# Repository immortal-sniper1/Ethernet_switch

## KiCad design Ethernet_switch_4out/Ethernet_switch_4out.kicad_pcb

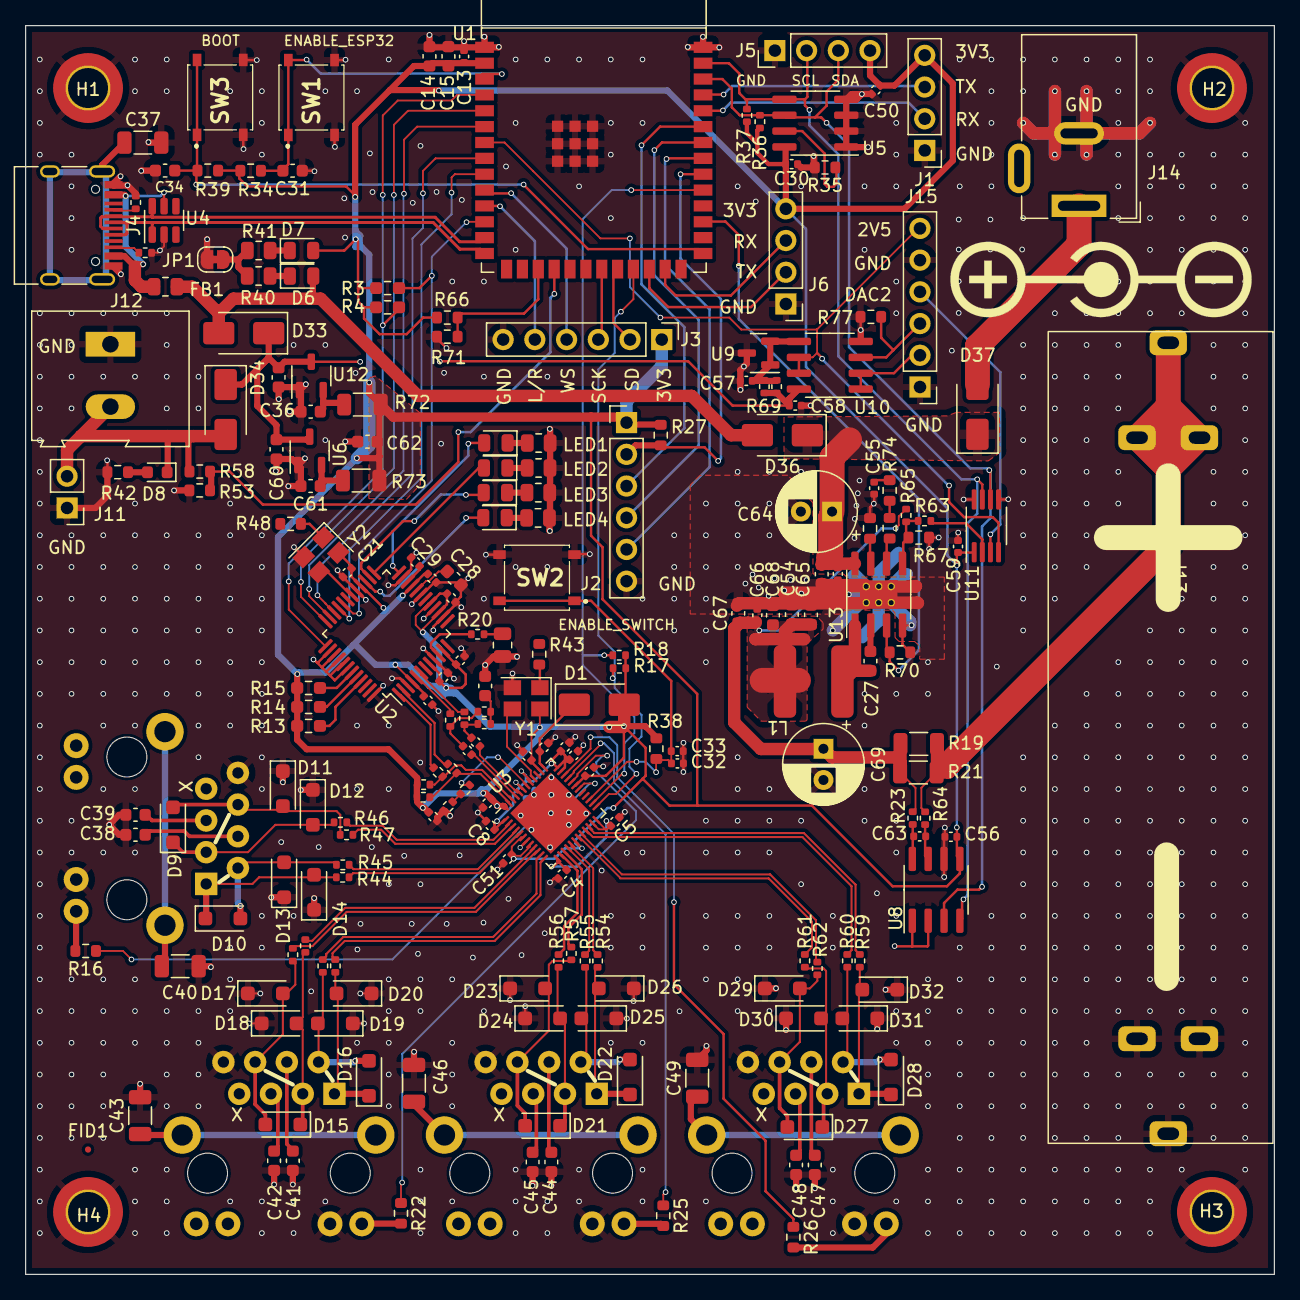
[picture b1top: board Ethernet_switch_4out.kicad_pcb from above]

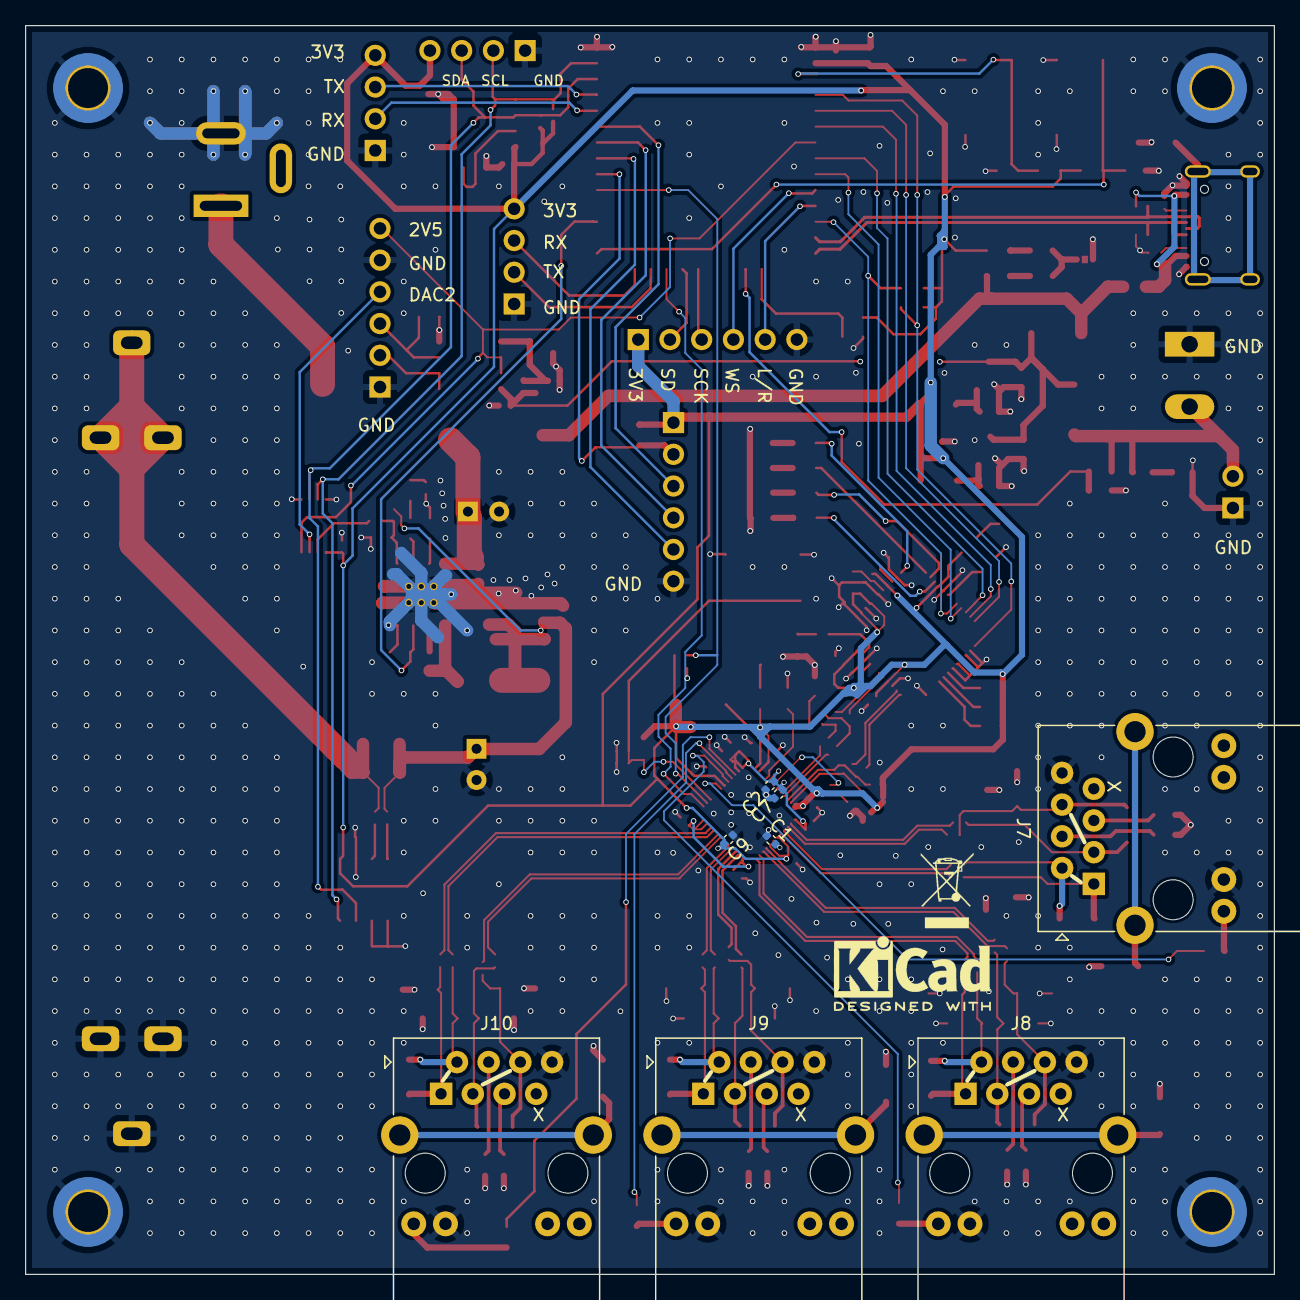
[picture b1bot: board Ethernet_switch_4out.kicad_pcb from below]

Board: 4 copper layers, 100.0 x 100.0 mm, 225 parts (10 on the bottom side), 151 nets.

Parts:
C1, C2, C3, C4, C5, C6, C7, C8, C9, C10, C11, C12, C13, C16, C17, C18, C19, C20, C21, C22, C25, C29, C30, C32, C33, C50, C51, C52, C56, C57, C58, C59, C66: 1u; C_0402_1005Metric
C14, C15, C28, C35, C36, C53, C54, C60, C61, C62, C65, C67, C68: 10u; C_0603_1608Metric
C23, C24: 6n8; C_0402_1005Metric
C26: 10n; C_0603_1608Metric
C27, C31, C34, C38, C39, C41, C42, C44, C45, C47, C48: 100n; C_0603_1608Metric
C37, C40, C43, C46, C49: 1n; C_1206_3216Metric
C55, C63: 4n7; C_0402_1005Metric
C64, C69: C_Polarized_Small; CP_Radial_D6.3mm_P2.50mm
D1, D33, D34, D36, D37: D_Schottky; D_SMA
D2, D3, D4, D5, D6, D7: green; LED_0805_2012Metric
D8: red; LED_0603_1608Metric
D9, D10, D11, D12, D13, D14, D15, D16, D17, D18, D19, D20, D21, D22, D23, D24, D25, D26, D27, D28, D29, D30, D31, D32: SMF6.0CA; D_SOD-123F
FB1: FerriteBead_Small; R_0805_2012Metric
FID1: Fiducial; Fiducial_0.5mm_Mask1mm
FID2: Fiducial; KiCad-Logo2_5mm_SilkScreen
FID3: Fiducial; WEEE-Logo_4.2x6mm_SilkScreen
FID4: Polarity; Polarity_Center_Positive_6mm_SilkScreen
H1, H2, H3, H4: hole; MountingHole_3.2mm_M3_DIN965_Pad_TopBottom
J1, J5, J6: Conn_01x04; PinHeader_1x04_P2.54mm_Vertical
J2, J3, J15: Conn_01x06; PinHeader_1x06_P2.54mm_Vertical
J4: USB_C_Receptacle; USB_C_Receptacle_HRO_TYPE-C-31-M-12
J7, J8, J9, J10: RJ45 Abracon ARJM11B1; RJ45_Abracon_ARJM11B1
J11: Conn_01x02; PinHeader_1x02_P2.54mm_Vertical
J12: Conn_01x02; TerminalBlock_Altech_AK300-2_P5.00mm
J13: Conn_01x02; MYOUNG MY-18650-01
J14: Jack-DC; BarrelJack_Wuerth_6941xx301002
JP1: Jumper_2_Bridged; SolderJumper-2_P1.3mm_Bridged_RoundedPad1.0x1.5mm
L1: 33u; SWPA6045S330MT
R1, R2, R9, R10: 49R9; R_0402_1005Metric
R3, R4, R13, R14, R15: 10k; R_0603_1608Metric_Pad0.98x0.95mm_HandSolder
R5, R6, R7, R8, R44, R45, R46, R47, R49, R50, R51, R52, R54, R55, R56, R57, R59, R60, R61, R62: 10; R_0402_1005Metric
R11, R69: 2k; R_0402_1005Metric
R12, R20, R68: 470; R_0402_1005Metric
R16, R22, R25, R26, R42: 1k; R_0603_1608Metric
R17, R18: 3k9; R_0402_1005Metric
R19, R21, R72, R73: 0R1; R_1206_3216Metric
R23, R64: 5R1; R_0402_1005Metric
R24: 12k; R_0805_2012Metric
R27, R34, R35, R38, R39, R53, R58, R66, R67, R70, R71, R74, R75: 10k; R_0603_1608Metric
R28, R29, R30, R31, R40, R41: 1k; R_0805_2012Metric
R32, R33, R36, R37: 5k1; R_0402_1005Metric
R43, R48: 2k; R_0603_1608Metric
R63, R65: 47k; R_0402_1005Metric
R76, R77: 120k; R_0603_1608Metric
SW1, SW2, SW3: MCU_RESET; PTS526SK15SMTR2LFS
U1: ESP32-S3-WROOM-1
U2: W5500; LQFP-48_7x7mm_P0.5mm
U3: RTL8305NB-VB-CG; QFN-48-1EP_6x6mm_P0.4mm_EP4.6x4.6mm
U4: SRV05-4; SOT-23-6
U5: CAT24C256; SOIC-8_3.9x4.9mm_P1.27mm
U6, U12: XC6206PxxxMR; SOT-23-3
U8: INA219AxD; SOIC-8_3.9x4.9mm_P1.27mm
U9: CJ431; SOT-23
U10: MCP6002-xSN; SOIC-8_3.9x4.9mm_P1.27mm
U11: AD5337; MSOP-8_3x3mm_P0.65mm
U13: RT7272B; SOIC-8-1EP_3.9x4.9mm_P1.27mm_EP2.29x3mm_ThermalVias
Y1, Y2: 25MHz; Crystal_SMD_3225-4Pin_3.2x2.5mm

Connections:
1V2: C1.2, C2.2, C3.2, C4.2, C5.2, C6.2, C7.2, C8.2, U3.1 (AVDDL), U3.7 (DVDDL), U3.13 (AVDDL), U3.23 (AVDDL), U3.24 (DVDDL), U3.35 (DVDDL), U3.36 (V12OUT), U3.41 (AVDDLPLL), U3.43 (AVDDL)
+3V3: C9.2, C10.2, C11.2, C12.2, C13.2, C14.1, C15.1, C17.2, C18.2, C19.2, C20.2, C21.2, C22.2, C25.2, C30.2, C50.2, C51.2, C56.2, C59.2, C62.1, D1.2 (A), D7.2 (A), J1.4, J2.1, J3.1, J5.4, J6.4, R1.2, R2.2, R3.1, R4.1, R13.2, R14.2, R15.2, R17.1, R18.1, R27.1, R34.1, R36.1, R37.1, R38.2, R39.2, R66.1, R72.1, R73.1, U1.2 (3V3), U2.4 (AVDD), U2.8 (AVDD), U2.11 (AVDD), U2.15 (AVDD), U2.17 (AVDD), U2.21 (AVDD), U2.28 (VDD), U3.6 (AVDDH), U3.8 (AVDDH), U3.18 (AVDDH), U3.31 (DVDDH), U3.38 (AVDDHPLL), U3.48 (AVDDH), U5.8 (VCC), U8.5 (VS), U11.1 (VDD), Y1.4, Y2.4
+5V: D6.2 (A), D33.2 (A), D36.2 (A), FB1.1
+BATT: D8.1 (K), D34.2 (A), J11.2, J12.2, R58.1
+VDC: C35.1, C58.2, C60.1, D33.1 (K), D34.1 (K), R68.2, R69.1, U6.3 (VI), U10.8 (V+), U12.3 (VI)
/2V5_RAW: C57.2, R68.1, R69.2, U9.1 (REF), U9.2 (K), U10.5 (+)
/Cell/BUCK_EN: R70.1, U1.29 (SPIIO7/GPIO36/FSPICLK/SUBSPICLK), U13.3 (EN)
/Cell/Buck_out: C54.1, C65.1, C66.2, C67.1, C68.1, C69.1, L1.2, R19.1, R21.1, R23.1, R65.2
/Cell/DAC1: R63.1, U11.2 (Vout_A)
/Cell/DAC2: J15.4, U11.3 (Vout_B)
/Cell/FB: R63.2, R65.1, R67.1, U13.5 (FB)
/Cell/Rlim: R76.1, U13.7 (RLIM)
/Cell/SW: C27.1, L1.1, U13.1 (SW)
/Cell/Vin_buck: C52.2, C53.1, C64.1, D36.1 (K), D37.1 (K), U13.8 (VIN)
/Cell/boot: C27.2, U13.2 (BOOT)
/Cell_V: R53.1, R58.2, U1.18 (GPIO10/TOUCH10/ADC1_CH9/FSPICS0/FSPIIO4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)
/ESP_BOOT: C34.1, R39.1, SW3.1 (A), U1.27 (GPIO0/BOOT)
/ESP_EN: C31.2, R34.2, SW1.1 (A), U1.3 (EN)
/L/R: J3.5, U1.11 (GPIO18/U1RXD/ADC2_CH7/CLK_OUT3)
/MISO: U1.8 (GPIO15/U0RTS/ADC2_CH4/XTAL_32K_P), U2.34 (MISO)
/MOSI: U1.6 (GPIO6/TOUCH6/ADC1_CH5), U2.35 (MOSI)
/Output_port1/GREEN: J8.9 (LEDG_A), R22.2
/Output_port1/L_RD+: D15.1 (A1), D18.2 (A2), J8.3 (RD+), R51.2
/Output_port1/L_RD-: D15.2 (A2), D17.2 (A2), J8.6 (RD-), R52.2
/Output_port1/L_TD+: D16.1 (A1), D20.2 (A2), J8.1 (TD+), R49.2
/Output_port1/L_TD-: D16.2 (A2), D19.2 (A2), J8.2 (TD-), R50.2
/Output_port1/RD+: R51.1, U3.9 (TXOP2)
/Output_port1/RD-: R52.1, U3.10 (TXON2)
/Output_port1/TD+: R49.1, U3.12 (RXOP2)
/Output_port1/TD-: R50.1, U3.11 (RXON2)
/Output_port2/GREEN: J9.9 (LEDG_A), R25.2
/Output_port2/L_RD+: D21.1 (A1), D24.2 (A2), J9.3 (RD+), R56.2
/Output_port2/L_RD-: D21.2 (A2), D23.2 (A2), J9.6 (RD-), R57.2
/Output_port2/L_TD+: D22.1 (A1), D26.2 (A2), J9.1 (TD+), R54.2
/Output_port2/L_TD-: D22.2 (A2), D25.2 (A2), J9.2 (TD-), R55.2
/Output_port2/RD+: R56.1, U3.14 (RXIP3)
/Output_port2/RD-: R57.1, U3.15 (RXIN3)
/Output_port2/TD+: R54.1, U3.17 (TXOP3)
/Output_port2/TD-: R55.1, U3.16 (TXON3)
/Output_port3/GREEN: J10.9 (LEDG_A), R26.2
/Output_port3/L_RD+: D27.1 (A1), D30.2 (A2), J10.3 (RD+), R61.2
/Output_port3/L_RD-: D27.2 (A2), D29.2 (A2), J10.6 (RD-), R62.2
/Output_port3/L_TD+: D28.1 (A1), D32.2 (A2), J10.1 (TD+), R59.2
/Output_port3/L_TD-: D28.2 (A2), D31.2 (A2), J10.2 (TD-), R60.2
/Output_port3/RD+: R61.1, U3.19 (TXOP4)
/Output_port3/RD-: R62.1, U3.20 (TXON4)
/Output_port3/TD+: R59.1, U3.22 (RXOP4)
/Output_port3/TD-: R60.1, U3.21 (RXON4)
/Output_port/GREEN: J7.9 (LEDG_A), R16.2
/Output_port/L_RD+: D9.1 (A1), D12.2 (A2), J7.3 (RD+), R46.2
/Output_port/L_RD-: D9.2 (A2), D11.2 (A2), J7.6 (RD-), R47.2
/Output_port/L_TD+: D10.1 (A1), D14.2 (A2), J7.1 (TD+), R44.2
/Output_port/L_TD-: D10.2 (A2), D13.2 (A2), J7.2 (TD-), R45.2
/Output_port/RD+: R46.1, U3.2 (RXIP1)
/Output_port/RD-: R47.1, U3.3 (RXIN1)
/Output_port/TD+: R44.1, U3.5 (TXIP1)
/Output_port/TD-: R45.1, U3.4 (TXIN1)
/Rail_V: R66.2, R71.1, U1.17 (GPIO9/TOUCH9/ADC1_CH8/FSPIHD/SUBSPIHD)
/SCK: J3.3, U1.21 (GPIO13/TOUCH13/ADC2_CH2/FSPIQ/FSPIIO7/S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)
/SCLK: U1.9 (GPIO16/U0CTS/ADC2_CH5/XTAL_32K_N), U2.33 (SCLK)
/SD: J3.2, U1.22 (GPIO14/TOUCH14/ADC2_CH3/FSPIWP/FSPIDQS/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)
/SWITCH_EN: C32.2, C33.2, R38.1, SW2.1 (A), U3.27 (RESET_B)
/W5500_LED1: D5.2 (A), U2.24 (SPDLED)
/W5500_LED2: D4.2 (A), U2.25 (LINKLED)
/W5500_LED3: D3.2 (A), U2.26 (DUPLED)
/W5500_LED4: D2.2 (A), U2.27 (ACTLED)
/WS: J3.4, U1.10 (GPIO17/U1TXD/ADC2_CH6)
/cc1: J4.A5 (CC1), R32.1
/cc2: J4.B5 (CC2), R33.1
/green_LED1: R16.1, U3.30 (P1LED)
/green_LED2: R22.1, U3.32 (P2LED/DIS_RST_BLNK)
/green_LED3: R25.1, U3.33 (P3LED)
/green_LED4: R26.1, U3.34 (P4LED)
/~INT: U1.5 (GPIO5/TOUCH5/ADC1_CH4), U2.36 (~INT)
/~RST: R4.2, U1.4 (GPIO4/TOUCH4/ADC1_CH3), U2.37 (~RST)
/~SCS: R3.2, U1.12 (GPIO8/TOUCH8/ADC1_CH7/SUBSPICS1), U2.32 (~SCS)
CLK_EXT: J2.3, U1.35 (MTMS/GPIO42)
D+: J4.A6 (D+), J4.B6 (D+), U1.14 (GPIO20/U1CTS/ADC2_CH9/CLK_OUT1/USB_D+), U4.1 (IO1)
D-: J4.A7 (D-), J4.B7 (D-), U1.13 (GPIO19/U1RTS/ADC2_CH8/CLK_OUT2/USB_D-), U4.6 (IO4)
GND: C1.1, C2.1, C3.1, C4.1, C5.1, C6.1, C7.1, C8.1, C9.1, C10.1, C11.1, C12.1, C13.1, C14.2, C15.2, C16.1, C17.1, C18.1, C19.1, C20.1, C21.1, C22.1, C25.1, C26.1, C28.1, C29.1, C30.1, C31.1, C32.1, C33.1, C34.2, C35.2, C36.2, C37.2, C38.1, C39.1, C40.2, C41.1, C42.1, C43.2, C44.1, C45.1, C46.2, C47.1, C48.1, C49.2, C50.1, C51.1, C52.1, C53.2, C54.2, C55.2, C56.1, C57.1, C58.1, C59.1, C60.2, C61.2, C62.2, C64.2, C65.2, C66.1, C67.2, C68.2, C69.2, D11.1 (A1), D12.1 (A1), D13.1 (A1), D14.1 (A1), D17.1 (A1), D18.1 (A1), D19.1 (A1), D20.1 (A1), D23.1 (A1), D24.1 (A1), D25.1 (A1), D26.1 (A1), D29.1 (A1), D30.1 (A1), D31.1 (A1), D32.1 (A1), H1.1, H2.1, H3.1, H4.1, J1.1, J2.6, J3.6, J4.A1 (GND), J4.A12 (GND), J4.B1 (GND), J4.B12 (GND), J5.1, J6.1, J7.8 (GND), J7.10 (LEDG_K), J8.8 (GND), J8.10 (LEDY_K), J9.8 (GND), J9.10 (LEDY_K), J10.8 (GND), J10.10 (LEDY_K), J11.1, J12.1, J13.2, J14.2, J15.1, J15.5, JP1.1 (A), R11.1, R24.2, R28.2, R29.2, R30.2, R31.2, R32.2, R33.2, R35.2, R42.1, R53.2, R67.2, R70.2, R71.2, R76.2, R77.2, SW1.2 (B), SW2.2 (B), SW3.2 (B), U1.1 (GND), U1.40 (GND), U1.41 (GND), U2.3 (AGND), U2.9 (AGND), U2.14 (AGND), U2.16 (AGND), U2.19 (AGND), U2.23 (RSVD), U2.29 (GND), U2.38 (RSVD), U2.39 (RSVD), U2.40 (RSVD), U2.41 (RSVD), U2.42 (RSVD), U2.48 (AGND), U3.49 (GND/EP), U4.2 (VN), U5.1 (A0), U5.2 (A1), U5.3 (A2), U5.4 (GND), U6.1 (GND), U8.1 (A1), U8.2 (A0), U8.6 (GND), U9.3 (A), U10.4 (V-), U11.5 (GND), U11.8 (A0), U12.1 (GND), U13.4 (GND), U13.9 (PAD), Y1.2, Y2.2
MISO_EXT: J2.5, U1.33 (MTDO/GPIO40/CLK_OUT2)
MOSI_EXT: J2.4, U1.34 (MTDI/GPIO41/CLK_OUT1)
unnamed: C23.1, R5.1, R10.2
unnamed: C24.1, R6.1, R9.2
unnamed: C26.2, R9.1, R10.1
unnamed: C55.1, R74.2
unnamed: C16.2, D1.1 (K), U3.37 (V33IN)
unnamed: D2.1 (K), R28.1
unnamed: D3.1 (K), R29.1
unnamed: D4.1 (K), R30.1
unnamed: D5.1 (K), R31.1
unnamed: D6.1 (K), R40.1
unnamed: D7.1 (K), R41.1
unnamed: D8.2 (A), R42.2
unnamed: D37.2 (A), J14.1
unnamed: J1.2, U1.36 (U0RXD/GPIO44/CLK_OUT2)
unnamed: J1.3, U1.37 (U0TXD/GPIO43/CLK_OUT1)
unnamed: C37.1, J4.S1 (SHIELD)
unnamed: C39.2, J7.5 (RCT)
unnamed: C40.1, J7.15 (SHIELD)
unnamed: C38.2, J7.4 (TCT)
unnamed: C42.2, J8.5 (RCT)
unnamed: C43.1, J8.15 (SHIELD)
unnamed: C41.2, J8.4 (TCT)
unnamed: C45.2, J9.5 (RCT)
unnamed: C46.1, J9.15 (SHIELD)
unnamed: C44.2, J9.4 (TCT)
unnamed: C48.2, J10.5 (RCT)
unnamed: C49.1, J10.15 (SHIELD)
unnamed: C47.2, J10.4 (TCT)
unnamed: J13.1, R19.2, R21.2, R64.1
unnamed: J15.2, U10.1, U10.2 (-)
unnamed: J15.3, R77.1, U10.3 (+)
unnamed: JP1.2 (B), R40.2, R41.2
unnamed: R11.2, R12.1
unnamed: R20.1, R24.1
unnamed: R43.2, Y1.1
unnamed: R48.2, Y2.1
unnamed: R74.1, R75.2
unnamed: C29.2, U2.22 (1V2O)
unnamed: R20.2, U2.10 (EXRES1)
unnamed: R13.1, U2.45 (PMODE0)
unnamed: R14.1, U2.44 (PMODE1)
unnamed: R15.1, U2.43 (PMODE2)
unnamed: R6.2, U2.5 (RXN)
unnamed: R5.2, U2.6 (RXP)
unnamed: C28.2, U2.20 (TOCAP)
unnamed: R7.2, U2.1 (TXN)
unnamed: R8.2, U2.2 (TXP)
unnamed: U2.30 (XI/CLKIN), Y2.3
unnamed: R12.2, U3.42 (IBREF)
unnamed: C24.2, U3.45 (RXIN0)
unnamed: C23.2, U3.44 (RXIP0)
unnamed: R1.1, R7.1, U3.46 (TXIN0)
unnamed: R2.1, R8.1, U3.47 (TXIP0)
unnamed: U3.40 (XI), Y1.3
unnamed: R35.1, U5.7 (WP)
unnamed: C61.1, R73.2, U6.2 (VO)
unnamed: C63.1, R23.2, U8.8 (IN+)
unnamed: C63.2, R64.2, U8.7 (IN-)
unnamed: C36.1, R72.2, U12.2 (VO)
unnamed: R75.1, U13.6 (COMP)
REF_2v5: J15.6, U1.7 (GPIO7/TOUCH7/ADC1_CH6), U10.6 (-), U10.7, U11.4 (REF)
RX: J6.3, U1.25 (GPIO48/SPICLK_N/SUBSPICLK_N_DIFF)
SCL: J5.2, R37.2, U1.39 (GPIO1/TOUCH1/ADC1_CH0), U5.5 (SDA), U8.4 (SCL), U11.7 (SCL)
SCL/MDC: R17.2, U1.23 (GPIO21), U3.25 (SCL/MDC)
SDA: J5.3, R36.2, U1.38 (GPIO2/TOUCH2/ADC1_CH1), U5.6 (SCL), U8.3 (SDA), U11.6 (SDA)
SDA/MDIO: R18.2, U1.31 (GPIO38/FSPIWP/SUBSPIWP), U3.26 (SDA/MDIO)
SS_EXT: J2.2, R27.2, U1.32 (MTCK/GPIO39/CLK_OUT3/SUBSPICS1)
TX: J6.2, U1.24 (GPIO47/SPICLK_P/SUBSPICLK_P_DIFF)
VBUS: FB1.2, J4.A4 (VBUS), J4.A9 (VBUS), J4.B4 (VBUS), J4.B9 (VBUS), U4.5 (VP)

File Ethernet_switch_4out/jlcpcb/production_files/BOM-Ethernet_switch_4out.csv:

Comment,Designator,Footprint,LCSC
FerriteBead_Small,FB1,R_0805_2012Metric,C1015
RT7272B,U13,SOIC-8-1EP_3.9x4.9mm_P1.27mm_EP2.29x3mm_ThermalVias,C127866
100n,"C27,C31,C34,C38,C39,C41,C42,C44,C45,C47,C48",C_0603_1608Metric,C14663
4n7,"C55,C63",C_0402_1005Metric,C1538
6n8,"C23,C24",C_0402_1005Metric,C1542
1k,"R28,R29,R30,R31,R40,R41",R_0805_2012Metric,C17513
10u,C28,C_0603_1608Metric,C19702
1k,"R16,R22,R25,R26,R42",R_0603_1608Metric,C21190
D_Schottky,"D1,D33,D34,D36,D37",D_SMA,C22452
red,D8,LED_0603_1608Metric,C2286
green,"D2,D3,D4,D5,D6,D7",LED_0805_2012Metric,C2297
5R1,"R23,R44,R45,R46,R47,R49,R5,R50,R51,R52,R54,R55,R56,R57,R59,R6,R60,R61,R62,R64,R7,R8",R_0402_1005Metric,C25077
470,"R12,R20,R68",R_0402_1005Metric,C25117
49R9,"R1,R10,R2,R9",R_0402_1005Metric,C25120
0R1,"R19,R21,R72,R73",R_1206_3216Metric,C25334
12k,R24,R_0805_2012Metric,C25752
47k,"R63,R65",R_0402_1005Metric,C25792
10k,"R13,R14,R15,R27,R3,R34,R35,R38,R39,R4,R53,R58,R66,R67,R70,R71,R74,R75",R_0603_1608Metric_Pad0.98x0.95mm_HandSolder,C25804
120k,"R76,R77",R_0603_1608Metric,C25808
5k1,"R32,R33,R36,R37",R_0402_1005Metric,C25905
ESP32-S3-WROOM-1,U1,ESP32-S3-WROOM-1,C2913204
SMF6.0CA,"D10,D11,D12,D13,D14,D15,D16,D17,D18,D19,D20,D21,D22,D23,D24,D25,D26,D27,D28,D29,D30,D31,D32,D9",D_SOD-123F,C2990473
RTL8305NB-VB-CG,U3,QFN-48-1EP_6x6mm_P0.4mm_EP4.6x4.6mm,C3010343
CJ431,U9,SOT-23,C3113
MCU_RESET,"SW1,SW2,SW3",PTS526SK15SMTR2LFS,C318884
USB_C_Receptacle,J4,USB_C_Receptacle_HRO_TYPE-C-31-M-12,C319148
W5500,U2,LQFP-48_7x7mm_P0.5mm,C32843
2k,"R11,R69",R_0402_1005Metric,C4109
AD5337,U11,MSOP-8_3x3mm_P0.65mm,C427645
3k9,"R17,R18",R_0402_1005Metric,C51721
1u,"C1,C10,C11,C12,C13,C16,C17,C18,C19,C2,C20,C21,C22,C25,C29,C3,C30,C32,C33,C4,C5,C50,C51,C52,C56,C57,C58,C59,C6,C66,C7,C8,C9",C_0402_1005Metric,C52923
XC6206PxxxMR,"U12,U6",SOT-23-3,C5446
10n,C26,C_0603_1608Metric,C57112
CAT24C256,U5,SOIC-8_3.9x4.9mm_P1.27mm,C6482
25MHz,"Y1,Y2",Crystal_SMD_3225-4Pin_3.2x2.5mm,C669088
MCP6002-xSN,U10,SOIC-8_3.9x4.9mm_P1.27mm,C7377
SRV05-4,U4,SOT-23-6,C85364
1n,"C37,C40,C43,C46,C49",C_1206_3216Metric,C9196
10u,"C14,C15,C35,C36,C53,C54,C60,C61,C62,C65,C67,C68",C_0603_1608Metric,C96446
Conn_01x02,J13,MYOUNG MY-18650-01,
C_Polarized_Small,C64,CP_Radial_D6.3mm_P2.50mm,
Conn_01x02,J12,TerminalBlock_Altech_AK300-2_P5.00mm,
Conn_01x02,J11,PinHeader_1x02_P2.54mm_Vertical,
INA219AxD,U8,SOIC-8_3.9x4.9mm_P1.27mm,
Conn_01x06,J3,PinHeader_1x06_P2.54mm_Vertical,
Conn_01x06,J15,PinHeader_1x06_P2.54mm_Vertical,
Conn_01x06,J2,PinHeader_1x06_P2.54mm_Vertical,
Jack-DC,J14,BarrelJack_Wuerth_6941xx301002,
33u,L1,SWPA6045S330MT,
C_Polarized_Small,C69,CP_Radial_D6.3mm_P2.50mm,
RJ45 Abracon ARJM11B1,J9,RJ45_Abracon_ARJM11B1,
RJ45 Abracon ARJM11B1,J8,RJ45_Abracon_ARJM11B1,
RJ45 Abracon ARJM11B1,J7,RJ45_Abracon_ARJM11B1,
RJ45 Abracon ARJM11B1,J10,RJ45_Abracon_ARJM11B1,

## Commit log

2024-07-20 xcel fix
